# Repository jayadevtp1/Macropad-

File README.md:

# My Macropad 

* My personal Macropad for AutoCAD, Blender works.
* It will help me for short cuts . 
* This is my first project.

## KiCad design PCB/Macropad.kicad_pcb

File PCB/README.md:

# PCB
* contains schematic,layer,kicad files

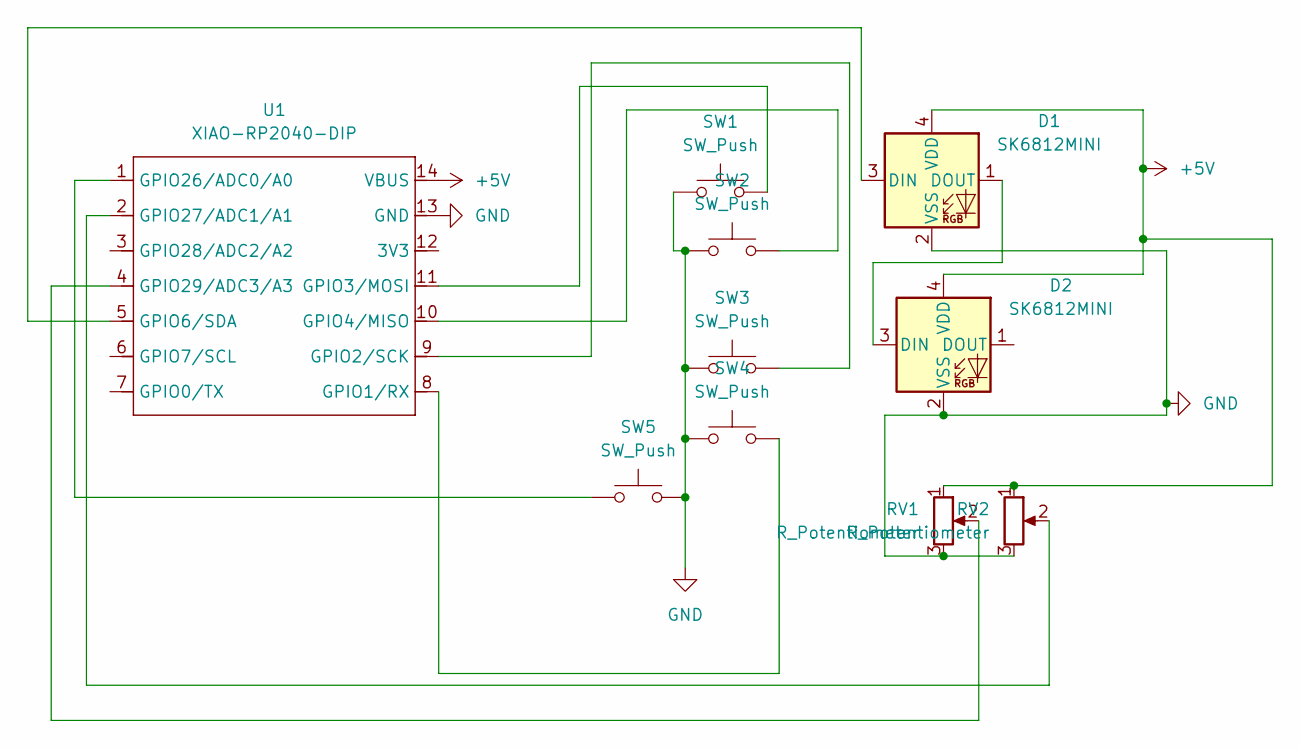
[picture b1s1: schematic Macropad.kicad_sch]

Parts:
D1, D2: SK6812MINI; LED_SK6812MINI_PLCC4_3.5x3.5mm_P1.75mm
RV1, RV2: R_Potentiometer; Potentiometer_Alpha_RD901F-40-00D_Single_Vertical
SW1, SW2, SW3, SW4, SW5: SW_Push; SW_Cherry_MX_1.00u_PCB
U1: XIAO-RP2040-DIP

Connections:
+5V: D1.4 (VDD), D2.4 (VDD), RV1.1, RV2.1, U1.14 (VBUS)
GND: D1.2 (VSS), D2.2 (VSS), RV1.3, RV2.3, SW1.1, SW2.1, SW3.1, SW4.1, SW5.2, U1.13 (GND)
unnamed: D1.3 (DIN), U1.5 (GPIO6/SDA)
unnamed: D1.1 (DOUT), D2.3 (DIN)
unnamed: SW4.2, U1.8 (GPIO1/RX)
unnamed: SW3.2, U1.9 (GPIO2/SCK)
unnamed: SW1.2, U1.11 (GPIO3/MOSI)
unnamed: SW2.2, U1.10 (GPIO4/MISO)
unnamed: SW5.1, U1.1 (GPIO26/ADC0/A0)
unnamed: RV2.2, U1.2 (GPIO27/ADC1/A1)
unnamed: RV1.2, U1.4 (GPIO29/ADC3/A3)

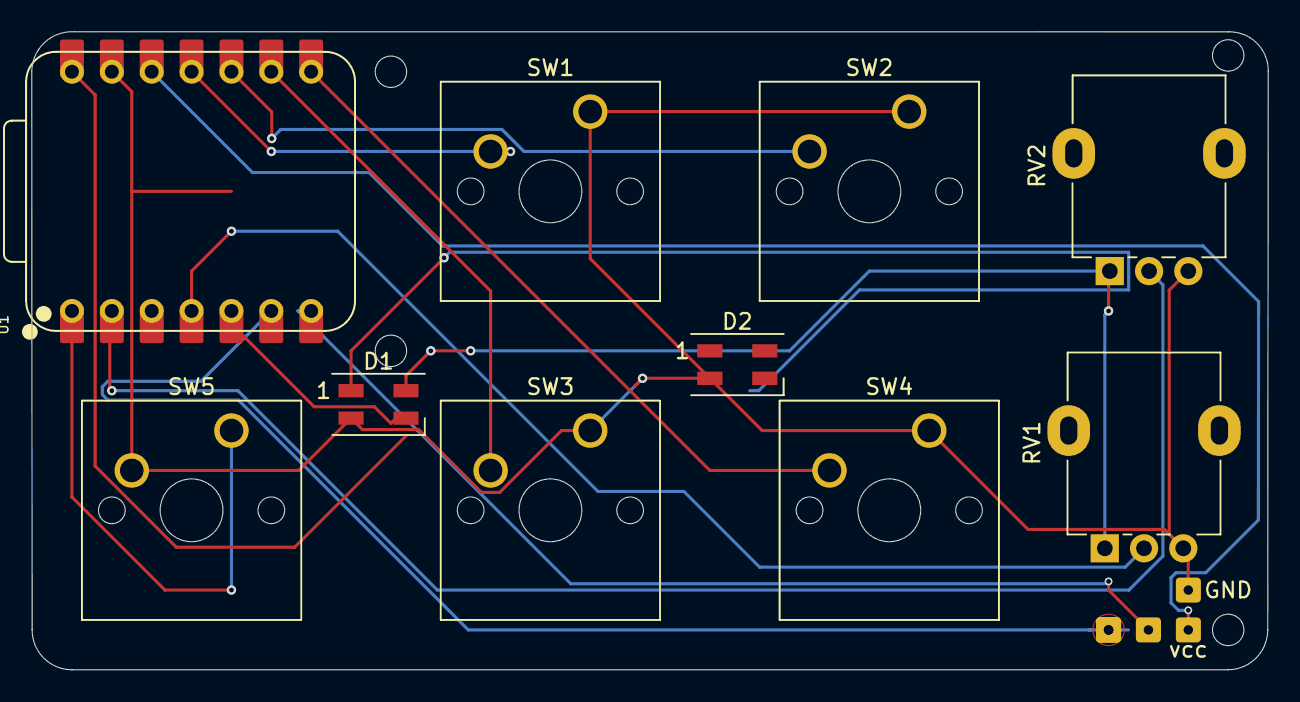
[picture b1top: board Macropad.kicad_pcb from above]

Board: 2 copper layers, 78.8 x 40.6 mm, 10 parts (0 on the bottom side), 11 nets.

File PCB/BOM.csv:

Designator,Val,Package,Mid X,Mid Y,Rotation,Layer
"D1","SK6812MINI","LED_SK6812MINI_PLCC4_3.5x3.5mm_P1.75mm",143.990000,-49.135000,0.000000,top
"D2","SK6812MINI","LED_SK6812MINI_PLCC4_3.5x3.5mm_P1.75mm",166.850000,-46.595000,0.000000,top
"RV1","R_Potentiometer","Potentiometer_Alpha_RD901F-40-00D_Single_Vertical",190.260000,-58.300000,90.000000,top
"RV2","R_Potentiometer","Potentiometer_Alpha_RD901F-40-00D_Single_Vertical",190.580000,-40.640000,90.000000,top
"SW1","SW_Push","SW_Cherry_MX_1.00u_PCB",157.480000,-30.480000,0.000000,top
"SW2","SW_Push","SW_Cherry_MX_1.00u_PCB",177.800000,-30.480000,0.000000,top
"SW3","SW_Push","SW_Cherry_MX_1.00u_PCB",157.480000,-50.800000,0.000000,top
"SW4","SW_Push","SW_Cherry_MX_1.00u_PCB",179.070000,-50.800000,0.000000,top
"SW5","SW_Push","SW_Cherry_MX_1.00u_PCB",134.620000,-50.800000,0.000000,top
"U1","XIAO-RP2040-DIP","XIAO-RP2040-DIP",132.080000,-35.560000,90.000000,top

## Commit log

2025-12-12 Create CAD
